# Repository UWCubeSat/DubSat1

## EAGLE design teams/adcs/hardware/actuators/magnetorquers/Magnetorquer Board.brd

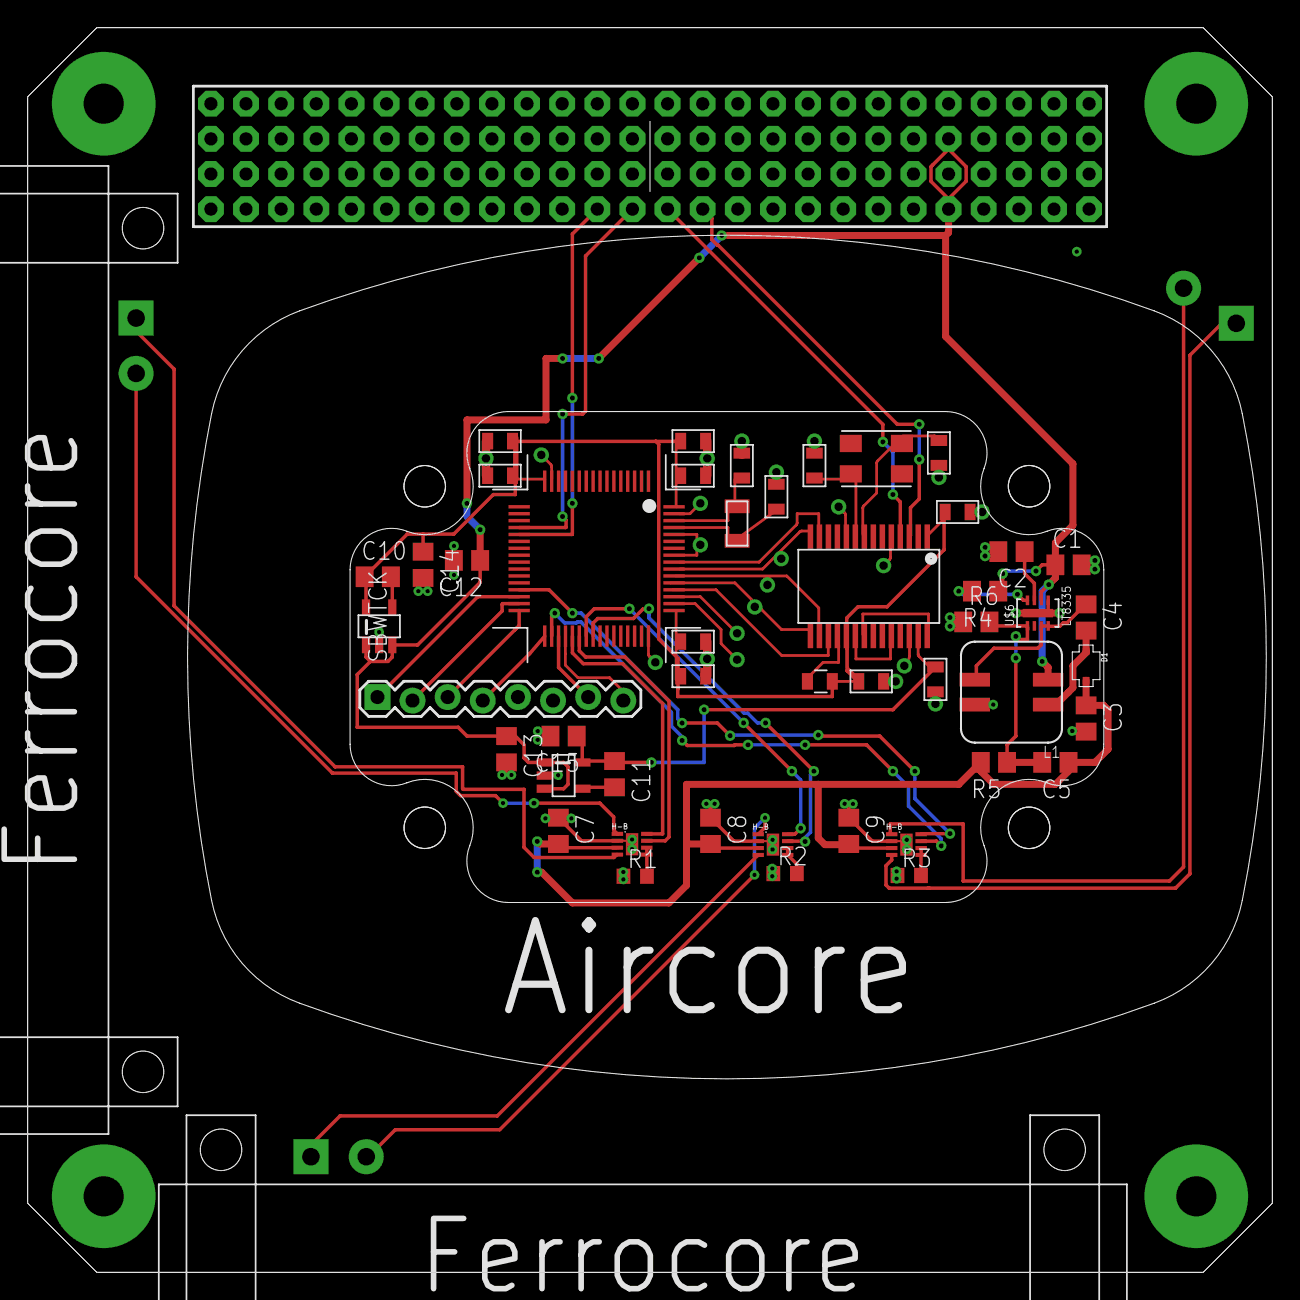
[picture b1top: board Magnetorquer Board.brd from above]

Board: 2 copper layers, 90.0 x 90.0 mm, 35 parts (0 on the bottom side), 37 nets.

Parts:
C1, C2, C3, C4, C5: C0805
C7, C8, C9: 10uF; C0805
C10, C11: 0.01 μF; C0805
C12, C13: 1 μF; C0805
C14, C15: 10 μF; C0805
D1: PMEG6010CEJ; SC-90
L1: WURTH_ELEKTRONIK_INDDD_744877001
LDO_3V3, LDO_5V: LINEAR_LDO_LT1761-X; SOT-23-5
R1, R2, R3: 1K; R0603
R4, R5, R6: R0805
U1, U2, U3: DFN-8EE
U$1: PC104_CONNECTOR
U$2: BOARD_TEMPLATE
U$3: MT_AIRCORE
U$4, U$5: MT_FERROCORE
U$6: LT8335; DDB
U$7: MSP-CAN_BLOCK
U$8: PROGRAM/DEBUG_PORT; 1X08_CONNECTOR

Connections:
6V: C3.1, C5.1, C7.2, C8.2, C9.2, D1.P$2, R5.2, U1.VDD, U2.VDD, U3.VDD
+3V3: C10.1, C14.1, LDO_3V3.P$5, U$7.3.3V@CAN1, U$7.3.3V@CAN2, U$7.3.3V@MSP1, U$7.3.3V@MSP2, U$7.3.3V_ANALOG@MSP2
+5V: C11.1, C15.1, LDO_5V.P$5, U$7.5V
CANH: U$1.P$53, U$7.CANH
CANL: U$1.P$57, U$7.CANL
EN_UVLO: R4.2, U$6.P$8
FBX: C5.2, R5.1, R6.2, U$6.P$1
GND: C1.2, C2.2, C3.2, C7.1, C8.1, C9.1, C12.2, C13.2, C14.2, C15.2, L1.P$2, LDO_3V3.P$2, LDO_5V.P$2, R1.1, R2.1, R3.1, R6.1, U1.GND@1, U1.GND@2, U2.GND@1, U2.GND@2, U3.GND@1, U3.GND@2, U$1.P$86, U$1.P$88, U$6.GND, U$6.P$5, U$7.GND@1, U$7.GND@2, U$7.GND@3, U$7.GND@4, U$7.GND@5, U$7.GND@7, U$7.GND@8, U$7.GND@9, U$7.GND@10, U$7.GND@11, U$7.GND@12, U$7.GND@13, U$7.GND@14, U$7.GND@15, U$7.GND@16, U$7.GND@17, U$7.GND@26, U$8.5, U$8.6
INT_VCC: C2.1, U$6.P$7
unnamed: R1.2, U1.VREF, U1.VSET
unnamed: R2.2, U2.VREF, U2.VSET
unnamed: C4.2, D1.P$1, L1.P$1
unnamed: R3.2, U3.VREF, U3.VSET
unnamed: U1.OUTB, U$4.B
unnamed: U1.OUTA, U$4.A
unnamed: U2.OUTA, U$5.A
unnamed: U2.OUTB, U$5.B
unnamed: U3.OUTB, U$3.B
unnamed: U3.OUTA, U$3.A
unnamed: C10.2, LDO_3V3.P$4
unnamed: U$7.SBWTCK, U$8.SBWTCK
unnamed: U$7.SBWTDIO, U$8.2
unnamed: U$7.P2.0_TXD, U$8.3
unnamed: U$7.P2.1_RXD, U$8.4
unnamed: U$7.P3.4_GPIO_DEBUG, U$8.7
unnamed: U$7.P3.5_GPIO_DEBUG, U$8.8
unnamed: C11.2, LDO_5V.P$4
PWM_X_1: U2.IN1, U$7.P1.7_GPIO/PWM
PWM_X_2: U2.IN2, U$7.P1.6_GPIO/PWM
PWM_Y_1: U1.IN1, U$7.P3.7_GPIO/PWM
PWM_Y_2: U1.IN2, U$7.P3.6_GPIO/PWM
PWM_Z_1: U3.IN1, U$7.P2.2_GPIO/PWM
PWM_Z_2: U3.IN2, U$7.P2.6_GPIO/PWM
SW: C4.1, L1.P$3, U$6.P$3, U$6.P$4
SYNC1: U$1.P$45, U$7.P7.2_SYNC1
SYNC2: U$1.P$49, U$7.PJ.3_SYNC2
VBAT: C1.1, C12.1, C13.1, L1.P$4, LDO_3V3.P$1, LDO_3V3.P$3, LDO_5V.P$1, LDO_5V.P$3, R4.1, U$1.P$85, U$1.P$87, U$6.P$6

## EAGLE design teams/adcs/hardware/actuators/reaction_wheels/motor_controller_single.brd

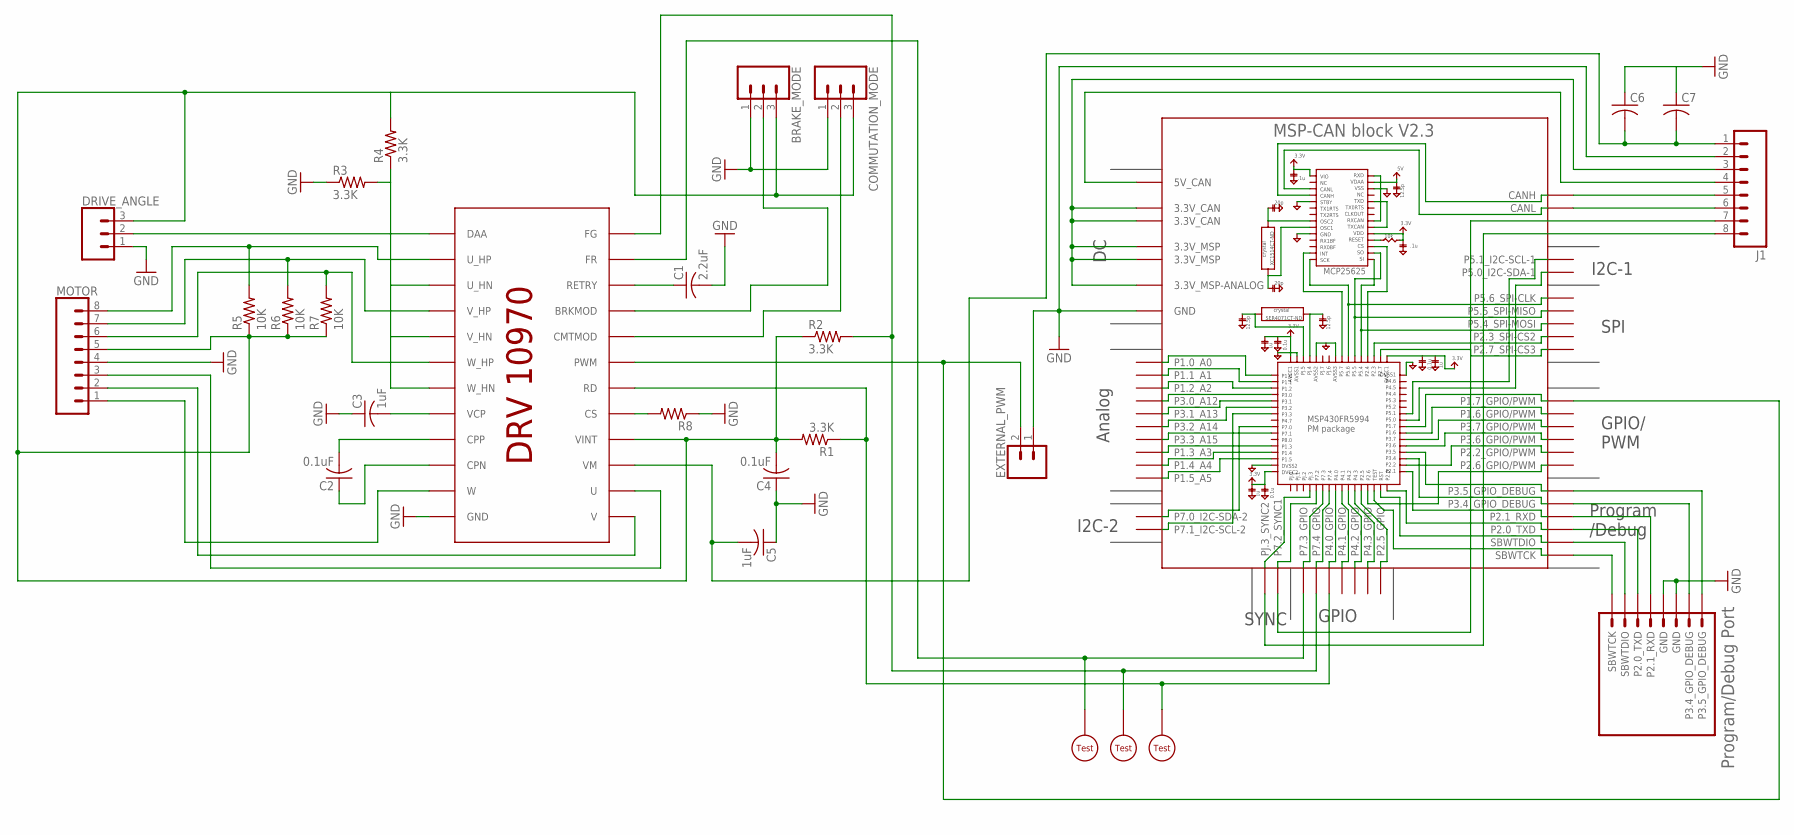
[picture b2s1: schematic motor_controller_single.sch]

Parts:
BRAKE_MODE: CONN_03LOCK; 1X03_LOCK
C1: 2.2uF; C1206
C2, C4: 0.1uF; C0805
C3, C5: 1uF; C1206
C6, C7: C-USC0805; C0805
COMMUTATION_MODE: CONN_03LOCK; 1X03_LOCK
DRIVE_ANGLE: CONN_03LOCK; 1X03_LOCK
EXTERNAL_PWM: CONN_02LOCK; 1X02_LOCK
J1: M08LOCK; 1X08_LOCK
MOTOR: CONN_08"; 1X08@1
R1, R2, R3, R4: 3.3K; R0805
R5, R6, R7: 10K; R0805
R8: R-US_R0805; R0805
U$1: DRV10970
U$2: MSP-CAN_BLOCK
U$3: PROGRAM/DEBUG_PORT; 1X08_CONNECTOR
U$4, U$5, U$6: KEYSTONE_SMD_TEST_POINT

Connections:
GND: BRAKE_MODE.1, C1.2, C3.1, C4.1, C5.1, C6.1, C7.1, COMMUTATION_MODE.1, DRIVE_ANGLE.1, EXTERNAL_PWM.1, J1.2, MOTOR.4, R3.1, R8.1, U$1.GND@1 (GND), U$1.GND@2 (GND), U$2.GND@1 (GND), U$2.GND@2 (GND), U$2.GND@3 (GND), U$2.GND@4 (GND), U$2.GND@5 (GND), U$2.GND@7 (GND), U$2.GND@8 (GND), U$2.GND@9 (GND), U$2.GND@10 (GND), U$2.GND@11 (GND), U$2.GND@12 (GND), U$2.GND@13 (GND), U$2.GND@14 (GND), U$2.GND@15 (GND), U$2.GND@16 (GND), U$2.GND@17 (GND), U$2.GND@26 (GND), U$3.5 (GND), U$3.6 (GND)
unnamed: C2.2, U$1.CPP
unnamed: C1.1, U$1.RETRY
unnamed: U$2.SBWTCK, U$3.SBWTCK
unnamed: U$2.SBWTDIO, U$3.2 (SBWTDIO)
unnamed: U$2.P2.0_TXD, U$3.3 (P2.0_TXD)
unnamed: U$2.P2.1_RXD, U$3.4 (P2.1_RXD)
unnamed: U$2.P3.4_GPIO_DEBUG, U$3.7 (P3.4_GPIO_DEBUG)
unnamed: U$2.P3.5_GPIO_DEBUG, U$3.8 (P3.5_GPIO_DEBUG)
unnamed: R1.1, U$1.RD, U$2.P4.0_GPIO, U$6.P$1
unnamed: EXTERNAL_PWM.2, U$1.PWM, U$2.P1.7_GPIO/PWM
unnamed: R2.2, U$1.FG, U$2.P7.4_GPIO, U$5.P$1
unnamed: U$1.FR, U$2.P7.3_GPIO, U$4.P$1
unnamed: C2.1, U$1.CPN
unnamed: J1.6, U$2.CANL
unnamed: C3.2, U$1.VCP
unnamed: C5.2, C6.2, C7.2, J1.1, U$1.VM
unnamed: R3.2, R4.1, U$1.U_HN, U$1.V_HN, U$1.W_HN
unnamed: DRIVE_ANGLE.2, U$1.DAA
unnamed: COMMUTATION_MODE.2, U$1.CMTMOD
unnamed: BRAKE_MODE.2, U$1.BRKMOD
unnamed: BRAKE_MODE.3, C4.2, COMMUTATION_MODE.3, DRIVE_ANGLE.3, MOTOR.5, R1.2, R2.1, R4.2, R5.1, R6.1, R7.1, U$1.VINT
unnamed: J1.5, U$2.CANH
unnamed: J1.4, U$2.5V (5V_CAN)
unnamed: J1.3, U$2.3.3V@CAN1 (3.3V_CAN), U$2.3.3V@CAN2 (3.3V_CAN), U$2.3.3V@MSP1 (3.3V_MSP), U$2.3.3V@MSP2 (3.3V_MSP), U$2.3.3V_ANALOG@MSP2 (3.3V_MSP-ANALOG)
unnamed: R8.2, U$1.CS
unnamed: MOTOR.1, U$1.W
unnamed: MOTOR.6, R7.2, U$1.W_HP
unnamed: MOTOR.7, R6.2, U$1.V_HP
unnamed: MOTOR.8, R5.2, U$1.U_HP
unnamed: MOTOR.2, U$1.V
unnamed: MOTOR.3, U$1.U
SYNC1: J1.7, U$2.P7.2_SYNC1
SYNC2: J1.8, U$2.PJ.3_SYNC2

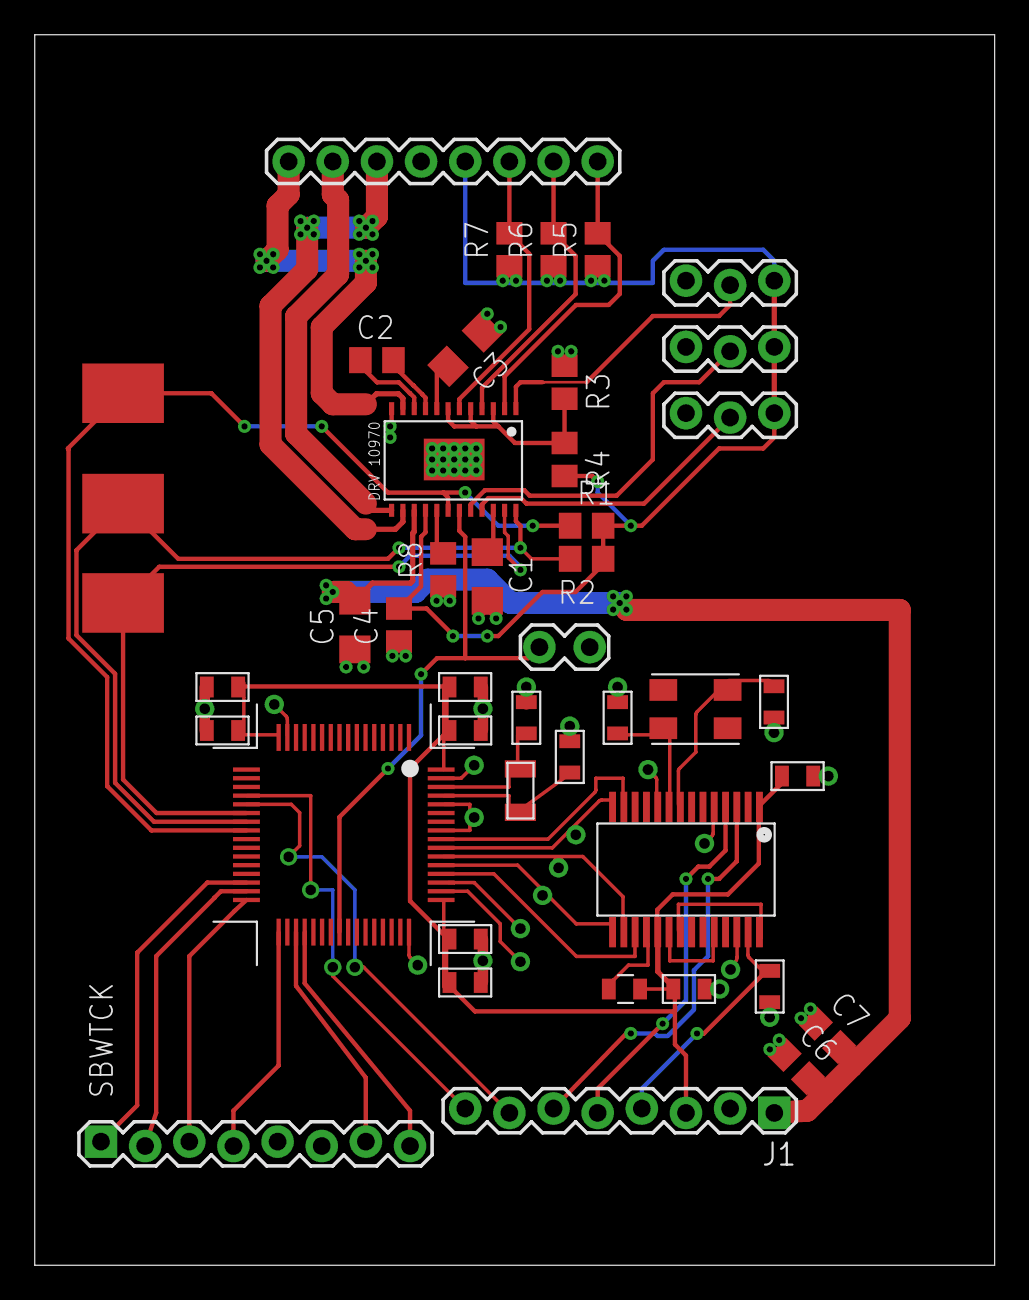
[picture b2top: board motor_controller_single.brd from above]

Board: 2 copper layers, 55.2 x 70.8 mm, 27 parts (0 on the bottom side), 34 nets.

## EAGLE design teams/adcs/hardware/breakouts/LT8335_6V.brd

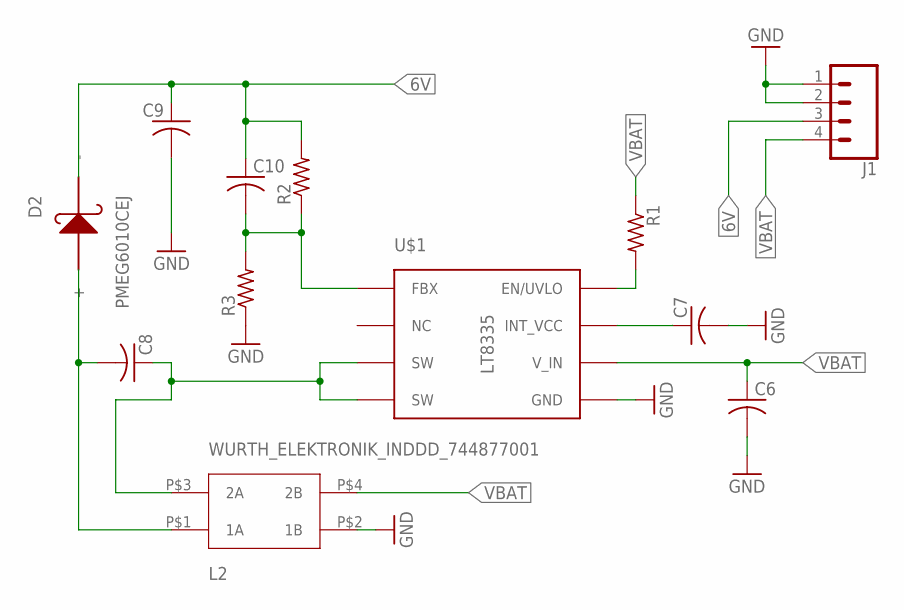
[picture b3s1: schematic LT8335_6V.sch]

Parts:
C6, C7, C8, C9, C10: C-USC0805; C0805
D2: PMEG6010CEJ; SC-90
J1: CONN_04LOCK; 1X04_LOCK
L2: WURTH_ELEKTRONIK_INDDD_744877001
R1, R2, R3: R-US_R0805; R0805
U$1: LT8335; DDB

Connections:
6V: C9.1, C10.1, D2.P$2 (-), J1.3, R2.2
EN_UVLO1: R1.2, U$1.P$8 (EN/UVLO)
FBX1: C10.2, R2.1, R3.2, U$1.P$1 (FBX)
GND: C6.2, C7.2, C9.2, J1.1, J1.2, L2.P$2 (1B), R3.1, U$1.GND, U$1.P$5 (GND)
INT_VCC1: C7.1, U$1.P$7 (INT_VCC)
unnamed: C8.2, D2.P$1 (+), L2.P$1 (1A)
SW1: C8.1, L2.P$3 (2A), U$1.P$3 (SW), U$1.P$4 (SW)
VBAT: C6.1, J1.4, L2.P$4 (2B), R1.1, U$1.P$6 (V_IN)

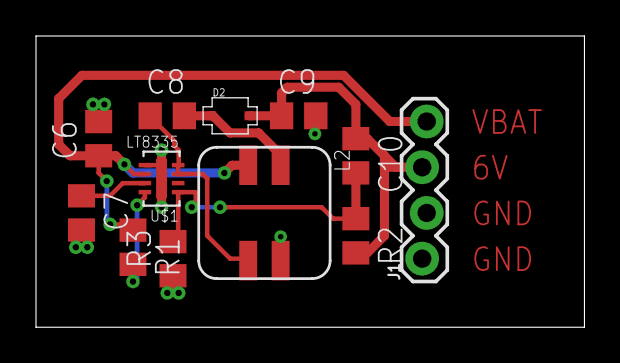
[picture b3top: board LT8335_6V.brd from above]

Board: 2 copper layers, 30.5 x 16.2 mm, 12 parts (0 on the bottom side), 8 nets.

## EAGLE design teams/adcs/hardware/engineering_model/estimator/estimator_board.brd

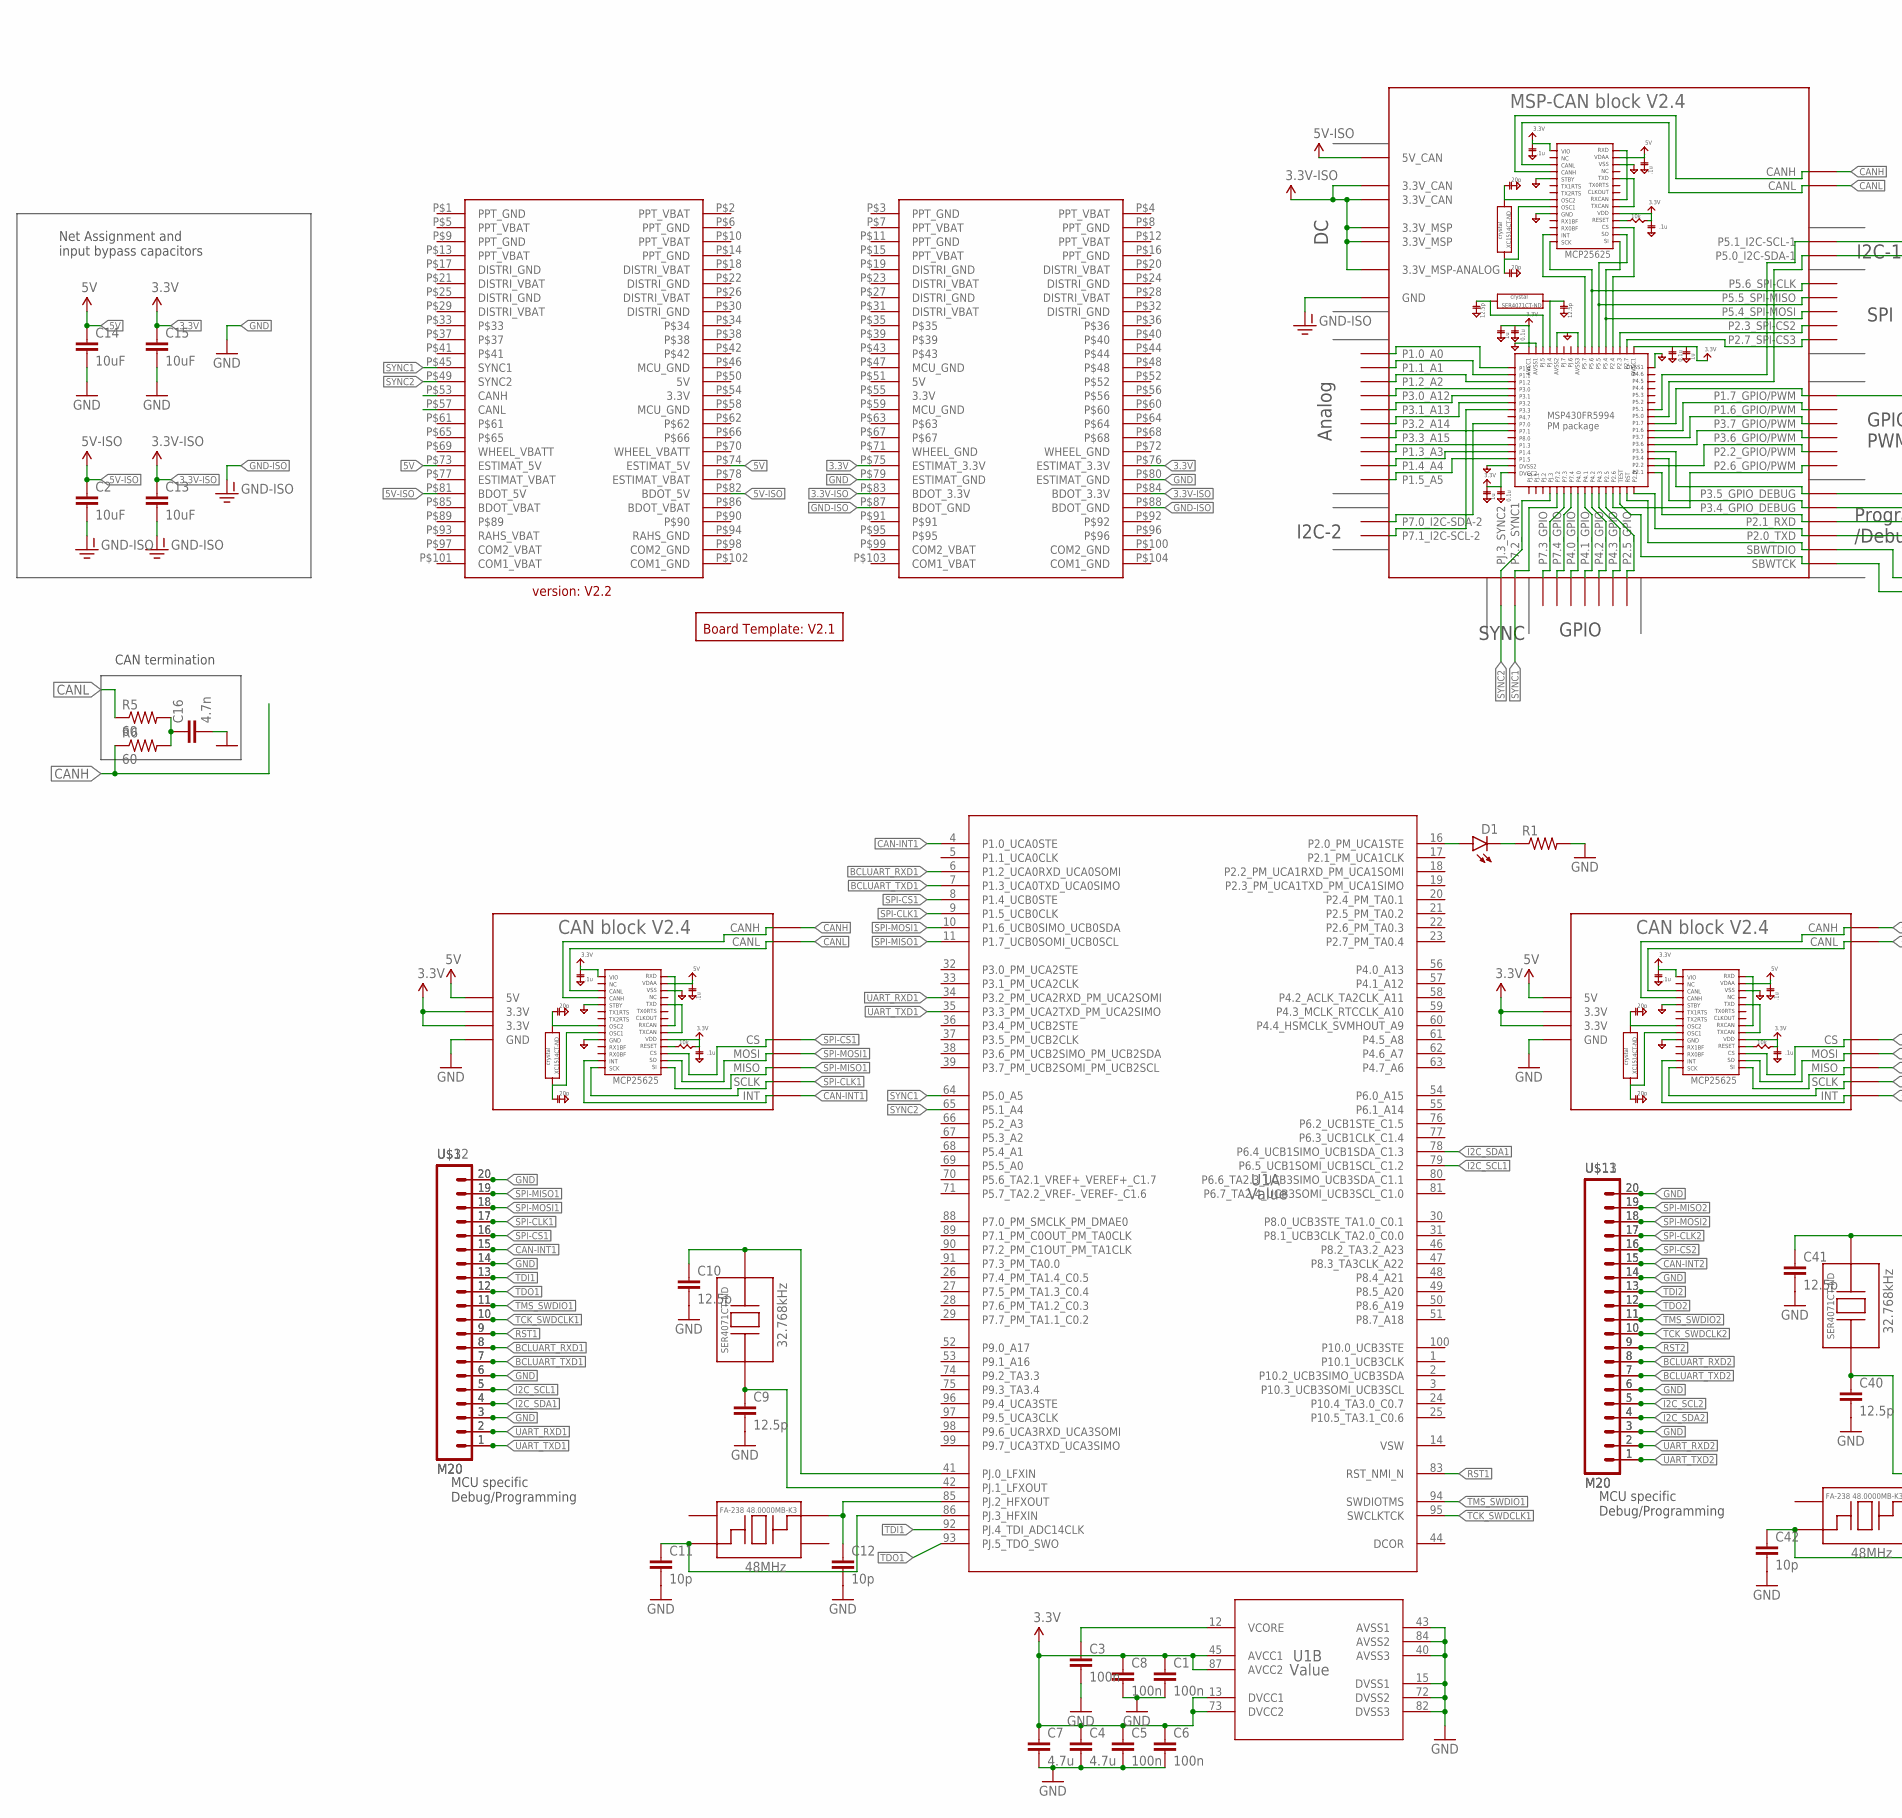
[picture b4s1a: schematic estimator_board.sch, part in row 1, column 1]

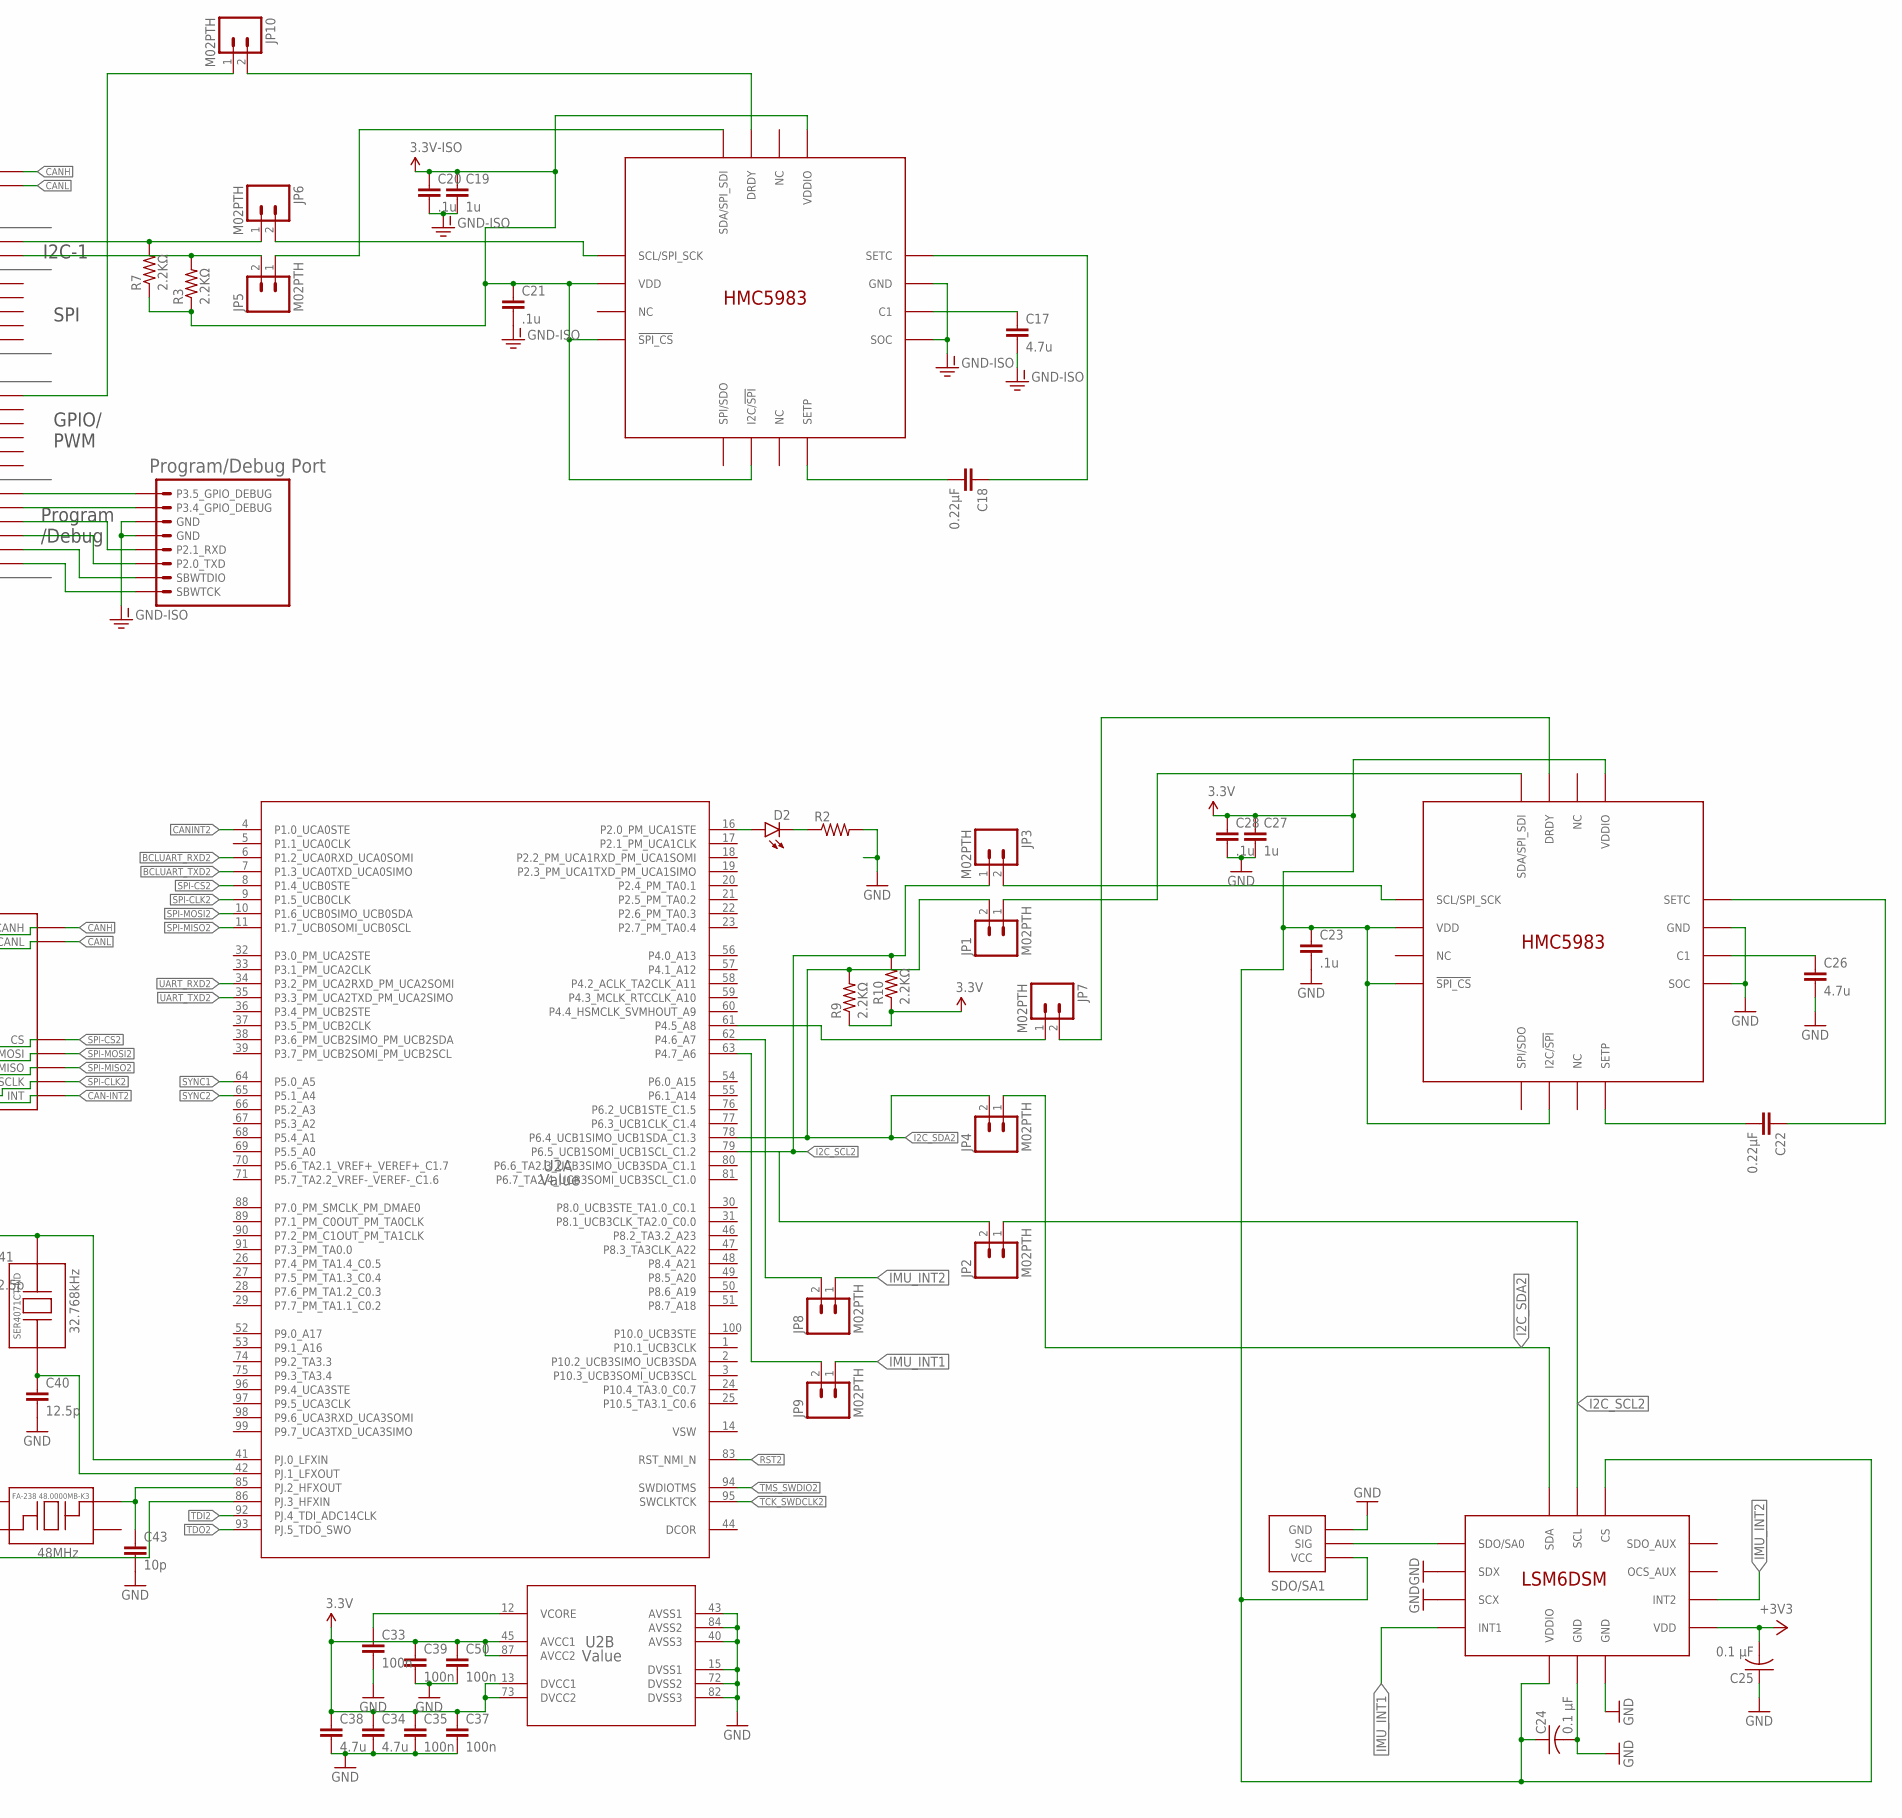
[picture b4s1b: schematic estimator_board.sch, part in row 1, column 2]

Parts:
C1, C3, C5, C6, C8, C33, C35, C37, C39, C50: 100n; 0805
C2, C13, C14, C15: 10uF; 0805
C4, C7, C17, C26, C34, C38: 4.7u; 0805
C9, C10, C40, C41: 12.5p; 0805
C11, C12, C42, C43: 10p; 0805
C16: 4.7n; 0805
C18, C22: 0.22µF; 0805
C19, C27: 1u; 0805
C20, C21, C23, C28: .1u; 0805
C24, C25: 0.1 μF; C0805
D1, D2: LED; LED-1206
JP1, JP2, JP3, JP4, JP5, JP6, JP7, JP8, JP9, JP10: M02PTH; 1X02
R1, R2: RESISTOR0805; 0805
R3, R7, R9, R10: 2.2KΩ; 0805
R5, R6: 60; 0805
SDO/SA1: 0_OHM_JUMPER
U1, U2: Value; PZ0100A_N
U$1, U$4: EPSON_CRYSTAL_FC-135R; FC-135R
U$2, U$9: EPSON_CRYSTAL_FA-238; FA-238
U$3, U$11, U$12, U$13: M20; 1X20
U$5: BOARD_TEMPLATE
U$6: PC104_CONNECTOR
U$7: MSP-CAN_BLOCK
U$8, U$10: CAN_BLOCK
U$14: PROGRAM/DEBUG_PORT; 1X08_CONNECTOR
U$15, U$18: HMC5983
U$17: LSM6DSM

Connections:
3.3V: C1.1, C4.1, C5.1, C6.1, C7.1, C8.1, C15.1, C23.1, C24.1, C25.2, C27.1, C28.1, C34.1, C35.1, C37.1, C38.1, C39.1, C50.1, R9.1, R10.1, SDO/SA1.P$3 (VCC), U1.13 (DVCC1), U1.45 (AVCC1), U1.73 (DVCC2), U1.87 (AVCC2), U2.13 (DVCC1), U2.45 (AVCC1), U2.73 (DVCC2), U2.87 (AVCC2), U$6.P$75 (ESTIMAT_3.3V), U$6.P$76 (ESTIMAT_3.3V), U$8.3.3V@CAN1 (3.3V), U$8.3.3V@CAN2 (3.3V), U$10.3.3V@CAN1 (3.3V), U$10.3.3V@CAN2 (3.3V), U$17.CS, U$17.VDD, U$17.VDDIO, U$18.!SPI_CS, U$18.I2C/!SPI, U$18.VDD, U$18.VDDIO
3.3V-ISO: C13.1, C19.1, C20.1, C21.1, R3.1, R7.1, U$6.P$83 (BDOT_3.3V), U$6.P$84 (BDOT_3.3V), U$7.3.3V@CAN1 (3.3V_CAN), U$7.3.3V@CAN2 (3.3V_CAN), U$7.3.3V@MSP1 (3.3V_MSP), U$7.3.3V@MSP2 (3.3V_MSP), U$7.3.3V_ANALOG@MSP2 (3.3V_MSP-ANALOG), U$15.!SPI_CS, U$15.I2C/!SPI, U$15.VDD, U$15.VDDIO
5V: C14.1, U$6.P$73 (ESTIMAT_5V), U$6.P$74 (ESTIMAT_5V), U$8.5V, U$10.5V
5V-ISO: C2.1, U$6.P$81 (BDOT_5V), U$6.P$82 (BDOT_5V), U$7.5V (5V_CAN)
BCLUART_RXD1: U1.6 (P1.2_UCA0RXD_UCA0SOMI), U$3.8, U$12.8
BCLUART_RXD2: U2.6 (P1.2_UCA0RXD_UCA0SOMI), U$11.8, U$13.8
BCLUART_TXD1: U1.7 (P1.3_UCA0TXD_UCA0SIMO), U$3.7, U$12.7
BCLUART_TXD2: U2.7 (P1.3_UCA0TXD_UCA0SIMO), U$11.7, U$13.7
CAN-INT1: U1.4 (P1.0_UCA0STE), U$3.15, U$8.INT, U$12.15
CAN-INT2: U$10.INT, U$11.15, U$13.15
CANH: R6.1, U$6.P$53 (CANH), U$7.CANH, U$8.CANH, U$10.CANH
CANINT2: U2.4 (P1.0_UCA0STE)
CANL: R5.1, U$6.P$57 (CANL), U$7.CANL, U$8.CANL, U$10.CANL
GND: C1.2, C3.2, C4.2, C5.2, C6.2, C7.2, C8.2, C9.2, C10.2, C11.2, C12.2, C14.2, C15.2, C16.2, C23.2, C24.2, C25.1, C26.2, C27.2, C28.2, C33.2, C34.2, C35.2, C37.2, C38.2, C39.2, C40.2, C41.2, C42.2, C43.2, C50.2, R1.2, R2.2, SDO/SA1.P$1 (GND), U1.15 (DVSS1), U1.40 (AVSS3), U1.43 (AVSS1), U1.72 (DVSS2), U1.82 (DVSS3), U1.84 (AVSS2), U2.15 (DVSS1), U2.40 (AVSS3), U2.43 (AVSS1), U2.72 (DVSS2), U2.82 (DVSS3), U2.84 (AVSS2), U$3.3, U$3.6, U$3.14, U$3.20, U$6.P$79 (ESTIMAT_GND), U$6.P$80 (ESTIMAT_GND), U$8.GND@1 (GND), U$8.GND@2 (GND), U$8.GND@3 (GND), U$8.GND@4 (GND), U$8.GND@5 (GND), U$8.GND@11 (GND), U$8.GND@12 (GND), U$8.GND@13 (GND), U$10.GND@1 (GND), U$10.GND@2 (GND), U$10.GND@3 (GND), U$10.GND@4 (GND), U$10.GND@5 (GND), U$10.GND@11 (GND), U$10.GND@12 (GND), U$10.GND@13 (GND), U$11.3, U$11.6, U$11.14, U$11.20, U$12.3, U$12.6, U$12.14, U$12.20, U$13.3, U$13.6, U$13.14, U$13.20, U$17.GND@1 (GND), U$17.GND@2 (GND), U$17.SCX, U$17.SDX, U$18.GND, U$18.SOC
GND-ISO: C2.2, C13.2, C17.2, C19.2, C20.2, C21.2, U$6.P$87 (BDOT_GND), U$6.P$88 (BDOT_GND), U$7.GND@1 (GND), U$7.GND@2 (GND), U$7.GND@3 (GND), U$7.GND@4 (GND), U$7.GND@5 (GND), U$7.GND@7 (GND), U$7.GND@8 (GND), U$7.GND@9 (GND), U$7.GND@10 (GND), U$7.GND@11 (GND), U$7.GND@12 (GND), U$7.GND@13 (GND), U$7.GND@14 (GND), U$7.GND@15 (GND), U$7.GND@16 (GND), U$7.GND@17 (GND), U$7.GND@26 (GND), U$14.5 (GND), U$14.6 (GND), U$15.GND, U$15.SOC
I2C_SCL1: U1.79 (P6.5_UCB1SOMI_UCB1SCL_C1.2), U$3.5, U$12.5
I2C_SCL2: JP2.1, JP2.2, JP3.1, R10.2, U2.79 (P6.5_UCB1SOMI_UCB1SCL_C1.2), U$11.5, U$13.5, U$17.SCL
I2C_SDA1: U1.78 (P6.4_UCB1SIMO_UCB1SDA_C1.3), U$3.4, U$12.4
I2C_SDA2: JP1.1, JP1.2, JP4.1, JP4.2, R9.2, U2.78 (P6.4_UCB1SIMO_UCB1SDA_C1.3), U$11.4, U$13.4, U$17.SDA, U$18.SDA/SPI_SDI
IMU_INT1: JP9.1, U$17.INT1
IMU_INT2: JP8.1, U$17.INT2
unnamed: D2.A, U2.16 (P2.0_PM_UCA1STE)
unnamed: D2.C, R2.1
unnamed: D1.A, U1.16 (P2.0_PM_UCA1STE)
unnamed: D1.C, R1.1
unnamed: U$7.P3.5_GPIO_DEBUG, U$14.8 (P3.5_GPIO_DEBUG)
unnamed: U$7.P3.4_GPIO_DEBUG, U$14.7 (P3.4_GPIO_DEBUG)
unnamed: C3.1, U1.12 (VCORE)
unnamed: C10.1, U1.41 (PJ.0_LFXIN), U$1.P$2
unnamed: C9.1, U1.42 (PJ.1_LFXOUT), U$1.P$1
unnamed: C12.1, U1.85 (PJ.2_HFXOUT), U$2.P$3
unnamed: C11.1, U1.86 (PJ.3_HFXIN), U$2.P$1
unnamed: U$7.P2.1_RXD, U$14.4 (P2.1_RXD)
unnamed: U$7.P2.0_TXD, U$14.3 (P2.0_TXD)
unnamed: U$7.SBWTDIO, U$14.2 (SBWTDIO)
unnamed: U$7.SBWTCK, U$14.SBWTCK
unnamed: JP5.1, U$15.SDA/SPI_SDI
unnamed: C16.1, R5.2, R6.2
unnamed: JP6.2, U$15.SCL/SPI_SCK
unnamed: C17.1, U$15.C1
unnamed: C18.2, U$15.SETP
unnamed: C18.1, U$15.SETC
unnamed: JP10.2, U$15.DRDY
unnamed: SDO/SA1.P$2 (SIG), U$17.SDO/SA0
unnamed: JP3.2, U$18.SCL/SPI_SCK
unnamed: JP6.1, R7.2, U$7.P5.1_I2C-SCL-1
unnamed: JP5.2, R3.2, U$7.P5.0_I2C-SDA-1
unnamed: JP8.2, U2.62 (P4.6_A7)
unnamed: JP7.1, U2.61 (P4.5_A8)
unnamed: JP10.1, U$7.P1.7_GPIO/PWM
unnamed: JP9.2, U2.63 (P4.7_A6)
unnamed: C26.1, U$18.C1
unnamed: C22.2, U$18.SETP
unnamed: C22.1, U$18.SETC
unnamed: JP7.2, U$18.DRDY
unnamed: C40.1, U2.42 (PJ.1_LFXOUT), U$4.P$1
unnamed: C41.1, U2.41 (PJ.0_LFXIN), U$4.P$2
unnamed: C42.1, U2.86 (PJ.3_HFXIN), U$9.P$1
unnamed: C43.1, U2.85 (PJ.2_HFXOUT), U$9.P$3
RST1: U1.83 (RST_NMI_N), U$3.9, U$12.9
RST2: U2.83 (RST_NMI_N), U$11.9, U$13.9
SPI-CLK1: U1.9 (P1.5_UCB0CLK), U$3.17, U$8.CLK (SCLK), U$12.17
SPI-CLK2: U2.9 (P1.5_UCB0CLK), U$10.CLK (SCLK), U$11.17, U$13.17
SPI-CS1: U1.8 (P1.4_UCB0STE), U$3.16, U$8.CS, U$12.16
SPI-CS2: U2.8 (P1.4_UCB0STE), U$10.CS, U$11.16, U$13.16
SPI-MISO1: U1.11 (P1.7_UCB0SOMI_UCB0SCL), U$3.19, U$8.MISO, U$12.19
SPI-MISO2: U2.11 (P1.7_UCB0SOMI_UCB0SCL), U$10.MISO, U$11.19, U$13.19
SPI-MOSI1: U1.10 (P1.6_UCB0SIMO_UCB0SDA), U$3.18, U$8.MOSI, U$12.18
SPI-MOSI2: U2.10 (P1.6_UCB0SIMO_UCB0SDA), U$10.MOSI, U$11.18, U$13.18
SYNC1: U1.64 (P5.0_A5), U2.64 (P5.0_A5), U$6.P$45 (SYNC1), U$7.P7.2_SYNC1
SYNC2: U1.65 (P5.1_A4), U2.65 (P5.1_A4), U$6.P$49 (SYNC2), U$7.PJ.3_SYNC2
TCK_SWDCLK1: U1.95 (SWCLKTCK), U$3.10, U$12.10
TCK_SWDCLK2: U2.95 (SWCLKTCK), U$11.10, U$13.10
TDI1: U1.92 (PJ.4_TDI_ADC14CLK), U$3.13, U$12.13
TDI2: U2.92 (PJ.4_TDI_ADC14CLK), U$11.13, U$13.13
TDO1: U1.93 (PJ.5_TDO_SWO), U$3.12, U$12.12
TDO2: U2.93 (PJ.5_TDO_SWO), U$11.12, U$13.12
TMS_SWDIO1: U1.94 (SWDIOTMS), U$3.11, U$12.11
TMS_SWDIO2: U2.94 (SWDIOTMS), U$11.11, U$13.11
UART_RXD1: U1.34 (P3.2_PM_UCA2RXD_PM_UCA2SOMI), U$3.2, U$12.2
UART_RXD2: U2.34 (P3.2_PM_UCA2RXD_PM_UCA2SOMI), U$11.2, U$13.2
UART_TXD1: U1.35 (P3.3_PM_UCA2TXD_PM_UCA2SIMO), U$3.1, U$12.1
UART_TXD2: U2.35 (P3.3_PM_UCA2TXD_PM_UCA2SIMO), U$11.1, U$13.1
VCORE: C33.1, U2.12 (VCORE)

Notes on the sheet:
MCU specific Debug/Programming
CAN termination
Net Assignment and input bypass capacitors

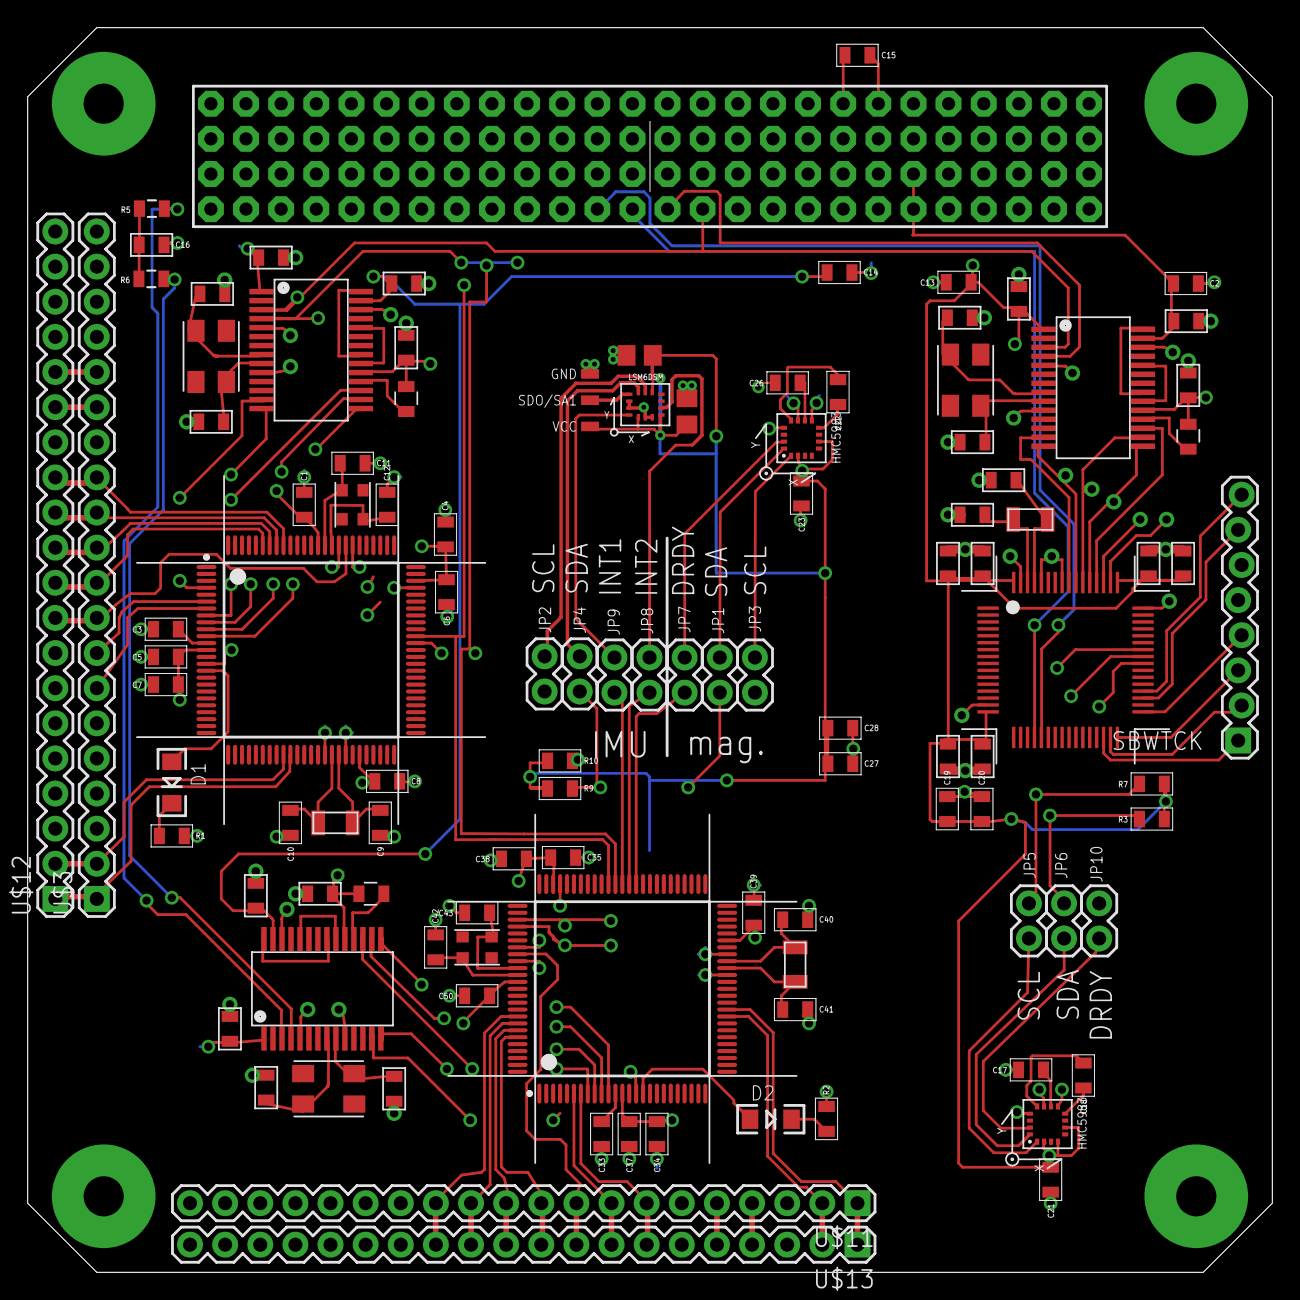
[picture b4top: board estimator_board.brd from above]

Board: 4 copper layers, 90.0 x 90.0 mm, 79 parts (0 on the bottom side), 83 nets.

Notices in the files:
parts and their libraries:
SparkFun-Connectors: Licensing: Creative Commons ShareAlike 4.0 International - https://creativecommons.org/licenses/by-sa/4.0
